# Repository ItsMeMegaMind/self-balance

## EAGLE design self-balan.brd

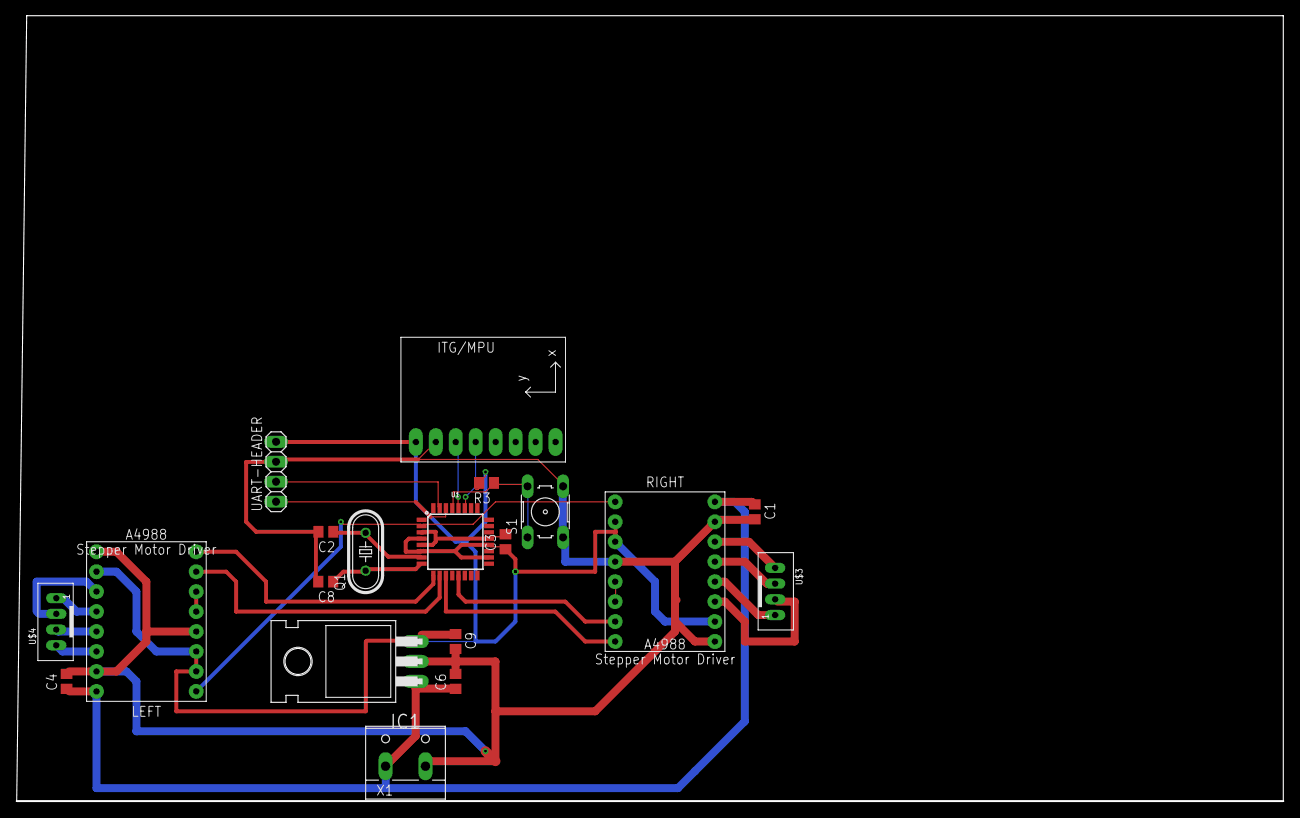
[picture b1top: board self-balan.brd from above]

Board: 2 copper layers, 161.3 x 100.0 mm, 19 parts (0 on the bottom side), 26 nets.

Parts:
C1, C4: 100u; C0805
C2, C3, C8: C0805
C6, C9: 10u; C0805
IC1: 7805T; TO220H
LEFT: A4988_STEP
Q1: HC49/S
R3: R0805
RIGHT: A4988_STEP
S1: B3F-10XX
U1: ATMEGA328P_TQFP; TQFP32-08
U2: GY-521MPU6050; GY-521
U$3, U$4: JST-PH_4-PIN_HEADER; JST_B4B-PH_HEADER
UART-HEADER: 1X04
X1: W237-132

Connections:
+5V: C3.1, C9.1, IC1.3, LEFT.MS1, LEFT.MS2, LEFT.VDD, R3.2, RIGHT.MS1, RIGHT.MS2, RIGHT.VDD, U1.4, U1.6, U1.18, U1.20, U2.VCC, UART-HEADER.4
D4: LEFT./EN, RIGHT./EN, U1.2
D5: LEFT.DIR, U1.9
D6: LEFT.STEP, U1.10
D7: RIGHT.DIR, U1.11
D9: RIGHT.STEP, U1.13
GND: C1.2, C2.2, C4.2, C6.2, C8.2, C9.2, IC1.2, LEFT.GND, LEFT.GND2, LEFT.MS3, RIGHT.GND, RIGHT.GND2, RIGHT.MS3, S1.3, S1.4, U2.GND, UART-HEADER.3, X1.2
unnamed: C2.1, Q1.2, U1.7
unnamed: C3.2, U1.3, U1.5, U1.21
unnamed: C8.1, Q1.1, U1.8
unnamed: RIGHT.2B, U$3.P4
unnamed: RIGHT.2A, U$3.P3
unnamed: RIGHT.1B, U$3.P2
unnamed: RIGHT.1A, U$3.P1
unnamed: LEFT.2B, U$4.P4
unnamed: LEFT.2A, U$4.P3
unnamed: RIGHT./RST, RIGHT./SLP
unnamed: LEFT.1B, U$4.P2
unnamed: LEFT.1A, U$4.P1
unnamed: LEFT./RST, LEFT./SLP
RST: R3.1, S1.1, S1.2, U1.29
RXD: U1.31, UART-HEADER.2
SCL: U1.28, U2.SCL
SDA: U1.27, U2.SDA
TXD: U1.30, UART-HEADER.1
VCC: C1.1, C4.1, C6.1, IC1.1, LEFT.VMOT, RIGHT.VMOT, X1.1

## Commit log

2019-03-14 Minor fix
2019-03-14 minor fixes
2019-03-14 Routing fixes
2019-03-14 Reouting fixed

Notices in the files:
parts and their libraries:
SparkFun-IC-Microcontroller: Licensing: Creative Commons ShareAlike 4.0 International - https://creativecommons.org/licenses/by-sa/4.0
